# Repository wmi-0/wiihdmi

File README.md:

# wiihdmi
HDMI for your Wii powered by GCVideo

This PCB is based on the popular GCVideo project as well as the Shuriken V3 schematics and features HDMI output (240p, 480i, 480p) for the Wii.
Menu navigation is possible via IR-remote or Gamecube controller.  
One of the main goals for this project was to keep it as cheap as possible.
This means no flex-cable for an easier install, no replacement of analog output (RGB/Component) and most importantly a 2-layer PCB design for cheap manufacturing.

**Consider this project as a beta for now.**  
I've spent several hours testing it on my launch-model Wii, but I'd like to hear some second opinions calling it ready for general use.

## Compatibility
### main_pcb_6_layer
Confirmed to work on RVL-CPU-01 boards.  
The layout possibly fits RVL-CPU-20 as well, but this is currently untested. Won't (properly) fit RVL-CPU-30.  

### main_pcb_4_layer
The new PCB layout is designed for 4-layer Wiis (RVL-CPU-40/50/60) but it's untested as of now.

Both designs use a 2-layer PCB layout which can be manufactured on the cheap, 4/6-layer is just the number of layers used on the intended target Wii mainboard.

## Install
See [GCVideo documentation](https://github.com/ikorb/gcvideo/blob/master/HDL/gcvideo_dvi/README-Wii.md#digital-audio-and-video)

## BOM
### Main PCB
| Designator  | Component |
| ------------- | ------------- |
| U1  | XC3S200A-4VQG100C  |
| U2  | M25P40  |
| U3  | TPS74012DGKR  |
| U4  | IRM-V538/TR1  |
| SW1  | EVQ9P701P  |
| J3  | 15 pin FFC connector 0.5mm pin pitch  |
| C1, C2  | 1 uF, 0805  |
| C3  | 10 uF, 0805  |
| C4-C12  | 0.1 uF, 0805  |
| R1, R3  | 4.7K, 0805  |
| R2  | 330, 0805  |

Use 0603 components for main_pcb_4_layer.

### HDMI PCB
| Designator  | Component |
| ------------- | ------------- |
| J1  | 15 pin FFC connector 0.5mm pin pitch  |
| J2  | Mini-HDMI (Type C) socket  |
| R1  | 180, 0402  |
| R2, R3  | 10K, 0402  |
| U1-U3  | TPD4S010 DQA (optional)  |

Use 0.8mm PCB thickness for both PCBs.

## Todos and next steps
- ~~PCB for 4-layer, 65nm Wii consoles (RVL-CPU-40+)~~
- ~~Provide better install pictures showing the current version of the PCB~~
- Switch to a more common 16 pin FFC instead of 15 pin
- Possibly add half-cut vias as anchor points (the initial design already had some, but the PCB manufacturer charged extra so I removed them again)
- KiCad project cleanup

## Acknowledgements
[ikorb](https://github.com/ikorb): GCVideo project  
[Steven Taffs](http://www.retro-system.com/shuriken%20video.htm): Shuriken V3 schematic and incredibly useful M25P40 programming tool  
[citrus3000psi](https://github.com/citrus3000psi): Inspiration from GCHDMI designs

## License
This project is licensed under the GPL v3.0 License - see the LICENSE.md file for details

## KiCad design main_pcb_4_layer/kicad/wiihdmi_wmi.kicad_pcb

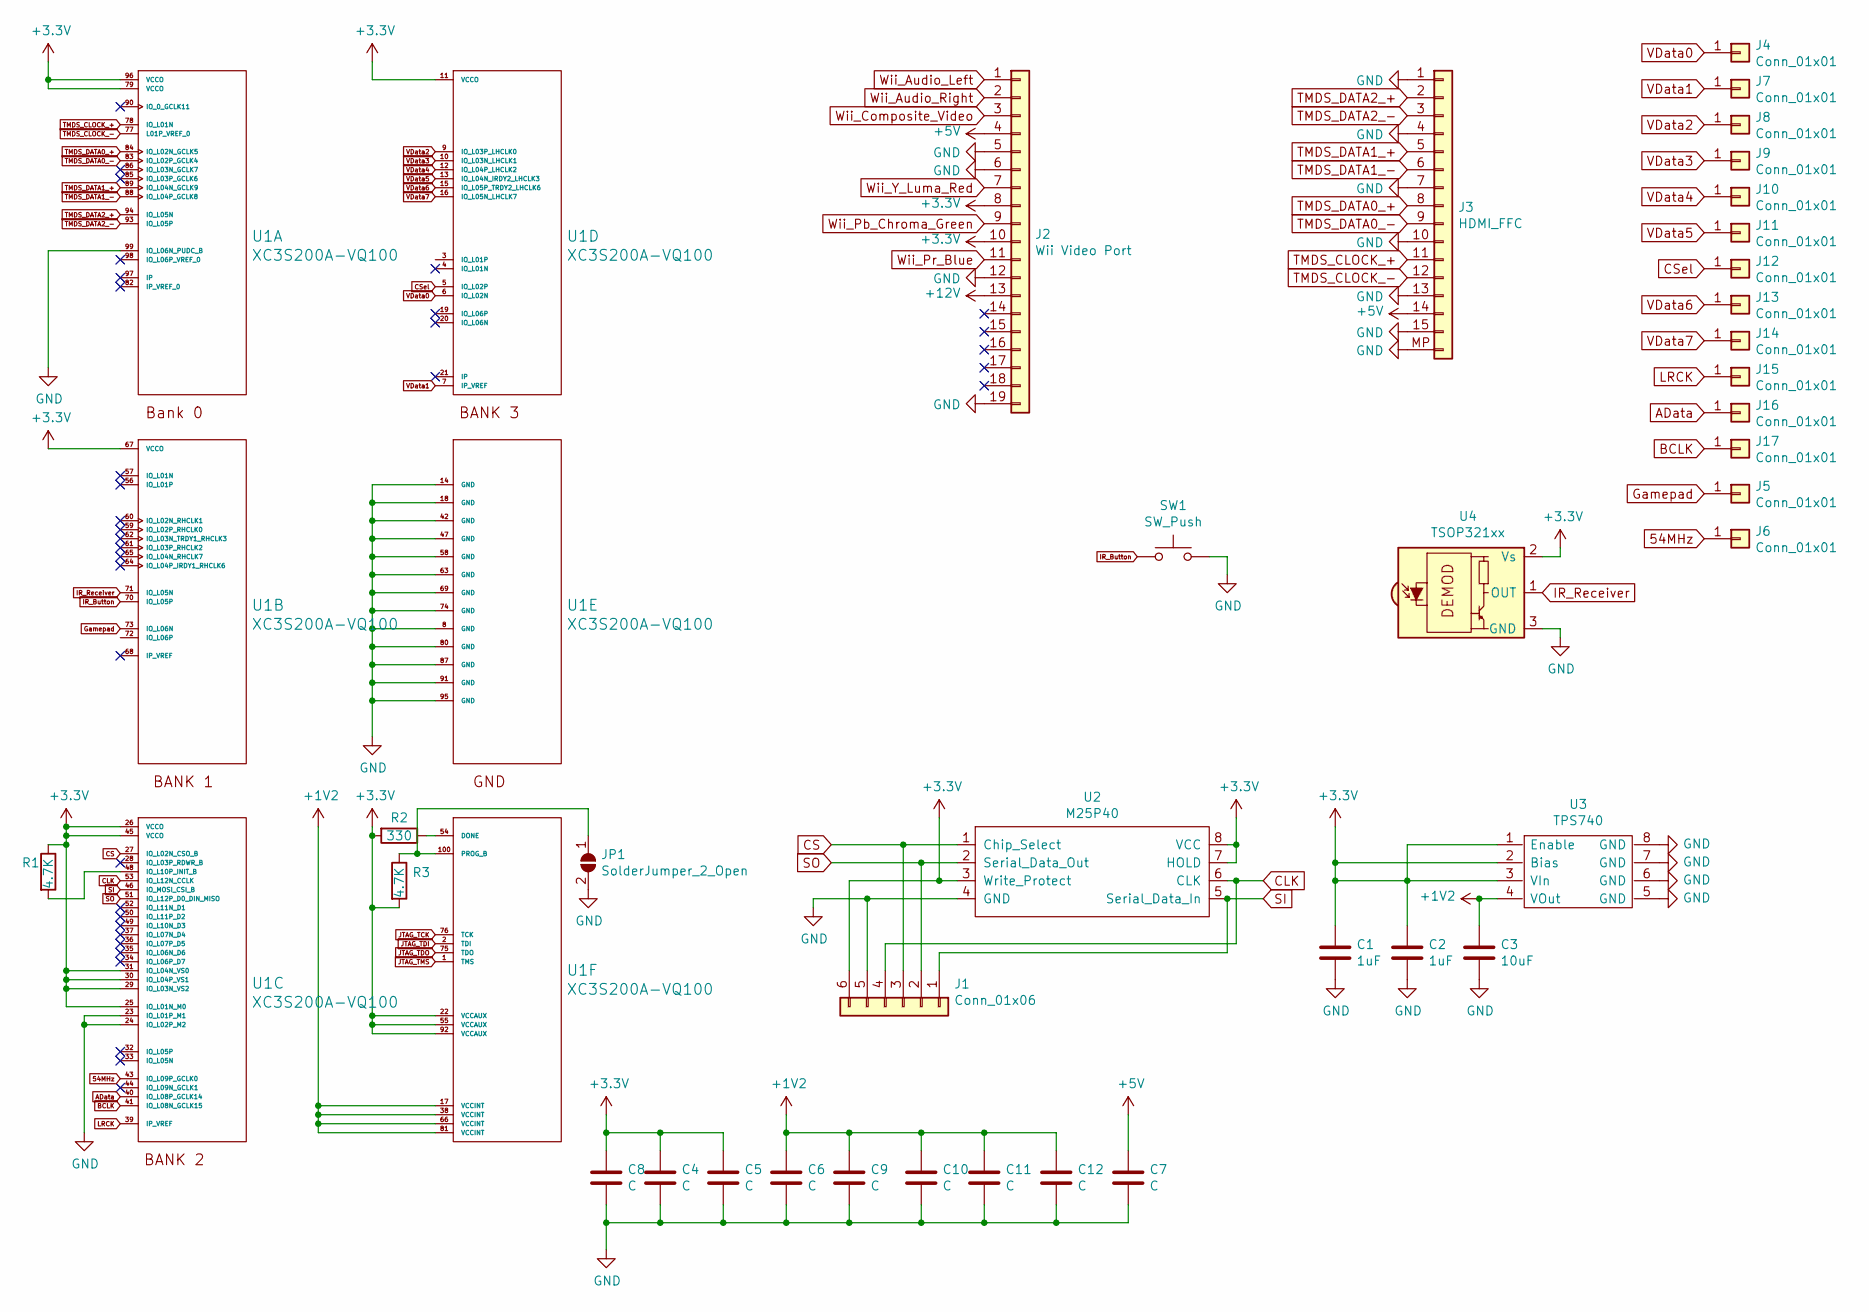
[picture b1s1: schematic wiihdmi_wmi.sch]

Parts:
C1, C2: 1uF; C_0805_2012Metric_Pad1.15x1.40mm_HandSolder
C3: 10uF; C_0805_2012Metric_Pad1.15x1.40mm_HandSolder
C4, C5, C6, C7, C8, C9, C10, C11, C12: C; C_0603_1608Metric_Pad1.05x0.95mm_HandSolder
J1: Conn_01x06; PinHeader_1x06_P1.27mm_Vertical_no_silk
J2: Wii Video Port; Wii AV Port
J3: HDMI_FFC; Hirose_FH12-15S-0.5SH_1x15-1MP_P0.50mm_Horizontal
J4, J5, J6, J7, J8, J9, J10, J11, J12, J13, J14, J15, J16, J17: Conn_01x01; TestPoint_Pad_1.0x1.0mm
JP1: SolderJumper_2_Open; SolderJumper-2_P1.3mm_Open_Pad1.0x1.5mm
R1, R3: 4.7K; R_0603_1608Metric_Pad1.05x0.95mm_HandSolder
R2: 330; R_0603_1608Metric_Pad1.05x0.95mm_HandSolder
SW1: SW_Push; EVQ9P701P
U1: XC3S200A-VQ100; xilinx_spartan3_virtex4_and_5-VQ100
U2: M25P40; SOIC-8_3.9x4.9mm_P1.27mm
U3: TPS740; MSOP-8_3x3mm_P0.65mm
U4: TSOP321xx; IRM-V5xx

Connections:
54MHz: J6.1, U1.43 (IO_L09P_GCLK0)
+1V2: C3.1, C6.1, C9.1, C10.1, C11.1, C12.1, U1.17 (VCCINT), U1.38 (VCCINT), U1.66 (VCCINT), U1.81 (VCCINT), U3.4 (VOut)
+3V3: C1.1, C2.1, C4.1, C5.1, C8.1, J1.6, J2.8, J2.10, R1.1, R2.2, R3.2, U1.11 (VCCO), U1.22 (VCCAUX), U1.25 (IO_L01N_M0), U1.26 (VCCO), U1.29 (IO_L03N_VS2), U1.30 (IO_L04P_VS1), U1.31 (IO_L04N_VS0), U1.45 (VCCO), U1.55 (VCCAUX), U1.67 (VCCO), U1.79 (VCCO), U1.92 (VCCAUX), U1.96 (VCCO), U2.3 (Write_Protect), U2.7 (HOLD), U2.8 (VCC), U3.1 (Enable), U3.2 (Bias), U3.3 (VIn), U4.2 (Vs)
+5V: C7.1, J2.4, J3.14
+12V: J2.13
AData: J16.1, U1.40 (IO_L08P_GCLK14)
BCLK: J17.1, U1.41 (IO_L08N_GCLK15)
CLK: J1.4, U1.53 (IO_L12N_CCLK), U2.6 (CLK)
CS: J1.3, U1.27 (IO_L02N_CSO_B), U2.1 (Chip_Select)
CSel: J12.1, U1.5 (IO_L02P)
GND: C1.2, C2.2, C3.2, C4.2, C5.2, C6.2, C7.2, C8.2, C9.2, C10.2, C11.2, C12.2, J1.5, J2.5, J2.6, J2.12, J2.19, J3.1, J3.4, J3.7, J3.10, J3.13, J3.15, J3.MP (Pin_16), JP1.2 (B), SW1.2, U1.8 (GND), U1.14 (GND), U1.18 (GND), U1.23 (IO_L01P_M1), U1.24 (IO_L02P_M2), U1.42 (GND), U1.47 (GND), U1.58 (GND), U1.63 (GND), U1.69 (GND), U1.74 (GND), U1.80 (GND), U1.87 (GND), U1.91 (GND), U1.95 (GND), U1.99 (IO_L06N_PUDC_B), U2.4 (GND), U3.5 (GND), U3.6 (GND), U3.7 (GND), U3.8 (GND), U4.3 (GND)
Gamepad: J5.1, U1.73 (IO_L06N); also elsewhere on the board
IR_Button: SW1.1, U1.70 (IO_L05P)
IR_Receiver: U1.71 (IO_L05N), U4.1 (OUT)
JTAG_TCK: U1.76 (TCK)
JTAG_TDI: U1.2 (TDI)
JTAG_TDO: U1.75 (TDO)
JTAG_TMS: U1.1 (TMS)
LRCK: J15.1, U1.39 (IP_VREF)
unnamed: JP1.1 (A), R3.1, U1.100 (PROG_B)
unnamed: R1.2, U1.48 (IO_L10P_INIT_B)
unnamed: R2.1, U1.54 (DONE)
SI: J1.1, U1.46 (IO_MOSI_CSI_B), U2.5 (Serial_Data_In)
SO: J1.2, U1.51 (IO_L12P_D0_DIN_MISO), U2.2 (Serial_Data_Out)
TMDS_CLOCK_+: J3.11, U1.78 (IO_L01N)
TMDS_CLOCK_-: J3.12, U1.77 (L01P_VREF_0)
TMDS_DATA0_+: J3.8, U1.84 (IO_L02N_GCLK5)
TMDS_DATA0_-: J3.9, U1.83 (IO_L02P_GCLK4)
TMDS_DATA1_+: J3.5, U1.89 (IO_L04N_GCLK9)
TMDS_DATA1_-: J3.6, U1.88 (IO_L04P_GCLK8)
TMDS_DATA2_+: J3.2, U1.94 (IO_L05N)
TMDS_DATA2_-: J3.3, U1.93 (IO_L05P)
VData0: J4.1, U1.6 (IO_L02N)
VData1: J7.1, U1.7 (IP_VREF)
VData2: J8.1, U1.9 (IO_L03P_LHCLK0)
VData3: J9.1, U1.10 (IO_L03N_LHCLK1)
VData4: J10.1, U1.12 (IO_L04P_LHCLK2)
VData5: J11.1, U1.13 (IO_L04N_IRDY2_LHCLK3)
VData6: J13.1, U1.15 (IO_L05P_TRDY2_LHCLK6)
VData7: J14.1, U1.16 (IO_L05N_LHCLK7)
Wii_Audio_Left: J2.1
Wii_Audio_Right: J2.2
Wii_Composite_Video: J2.3
Wii_Pb_Chroma_Green: J2.9
Wii_Pr_Blue: J2.11
Wii_Y_Luma_Red: J2.7

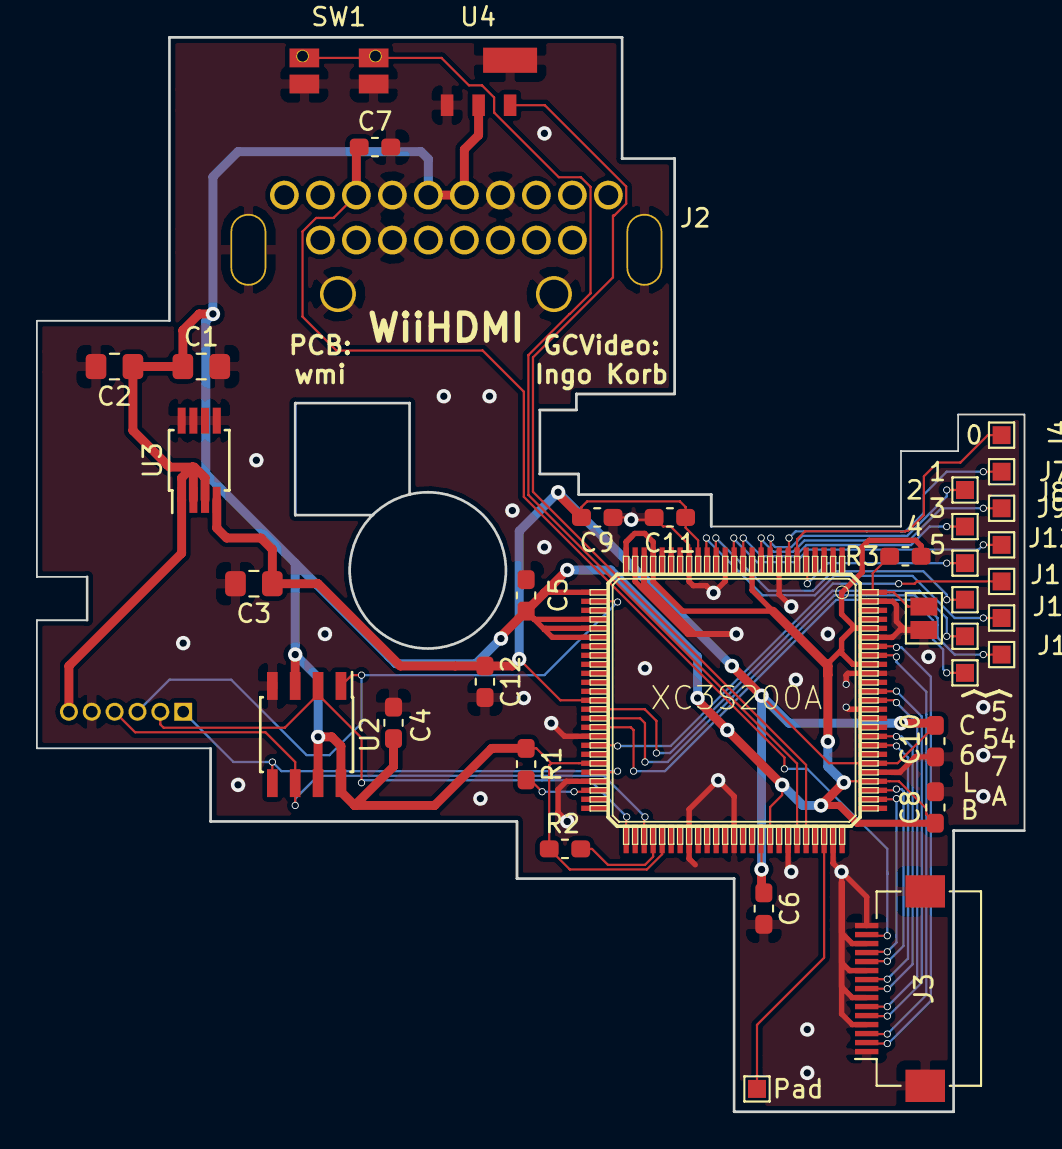
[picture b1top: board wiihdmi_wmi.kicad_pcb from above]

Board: 2 copper layers, 54.9 x 59.7 mm, 38 parts (0 on the bottom side), 35 nets.

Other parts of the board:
Pad: Conn_01x01; TestPoint_Pad_1.0x1.0mm

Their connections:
Gamepad: Pad.1; also elsewhere on the board

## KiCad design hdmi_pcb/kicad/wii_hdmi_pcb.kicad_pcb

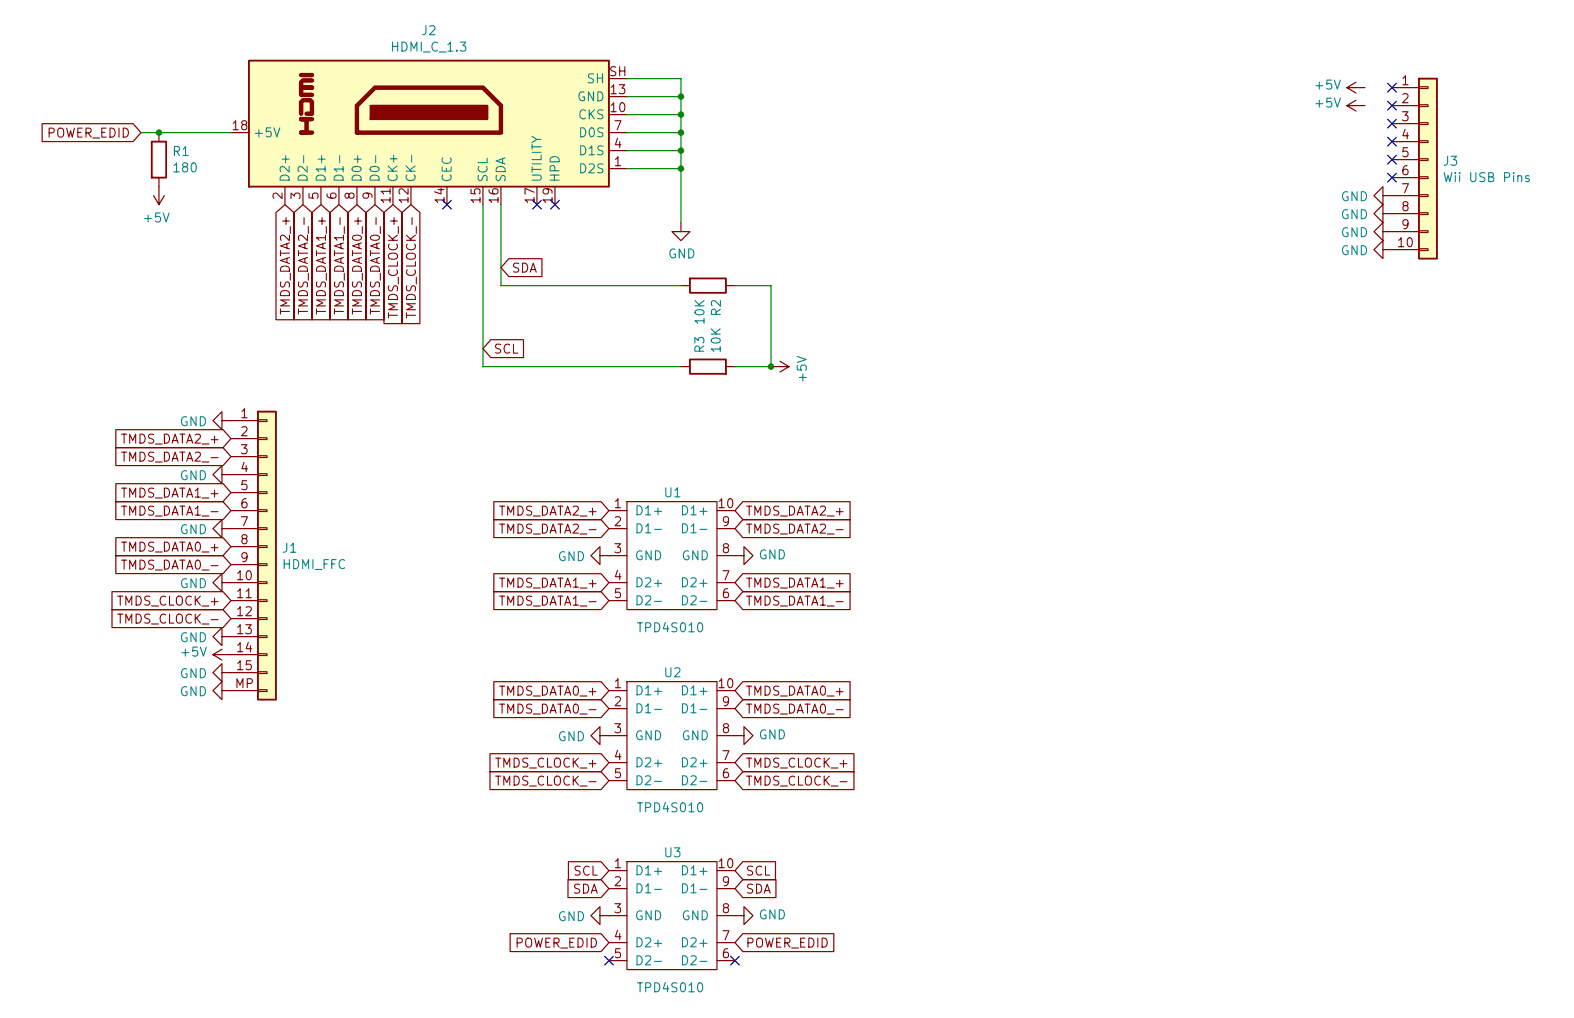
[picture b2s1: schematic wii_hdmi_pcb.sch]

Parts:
J1: HDMI_FFC; Hirose_FH12-15S-0.5SH_1x15-1MP_P0.50mm_Horizontal
J2: HDMI_C_1.3; HDMI Type C
J3: Wii USB Pins; Wii USB Port
R1: 180; R_0402_1005Metric
R2, R3: 10K; R_0402_1005Metric
U1, U2, U3: TPD4S010; TPD4S010 DQA

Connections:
+5V: J1.14, R1.2, R2.1, R3.2
GND: J1.1, J1.4, J1.7, J1.10, J1.13, J1.15, J1.MP (Pin_16), J2.1 (D2S), J2.4 (D1S), J2.7 (D0S), J2.10 (CKS), J2.13 (GND), J2.SH, J3.7, J3.8, J3.9, J3.10, U1.3 (GND), U1.8 (GND), U2.3 (GND), U2.8 (GND), U3.3 (GND), U3.8 (GND)
POWER_EDID: J2.18 (+5V), R1.1, U3.4 (D2+), U3.7 (D2+)
SCL: J2.15 (SCL), R3.1, U3.1 (D1+), U3.10 (D1+)
SDA: J2.16 (SDA), R2.2, U3.2 (D1-), U3.9 (D1-)
TMDS_CLOCK_+: J1.11, J2.11 (CK+), U2.4 (D2+), U2.7 (D2+)
TMDS_CLOCK_-: J1.12, J2.12 (CK-), U2.5 (D2-), U2.6 (D2-)
TMDS_DATA0_+: J1.8, J2.8 (D0+), U2.1 (D1+), U2.10 (D1+)
TMDS_DATA0_-: J1.9, J2.9 (D0-), U2.2 (D1-), U2.9 (D1-)
TMDS_DATA1_+: J1.5, J2.5 (D1+), U1.4 (D2+), U1.7 (D2+)
TMDS_DATA1_-: J1.6, J2.6 (D1-), U1.5 (D2-), U1.6 (D2-)
TMDS_DATA2_+: J1.2, J2.2 (D2+), U1.1 (D1+), U1.10 (D1+)
TMDS_DATA2_-: J1.3, J2.3 (D2-), U1.2 (D1-), U1.9 (D1-)

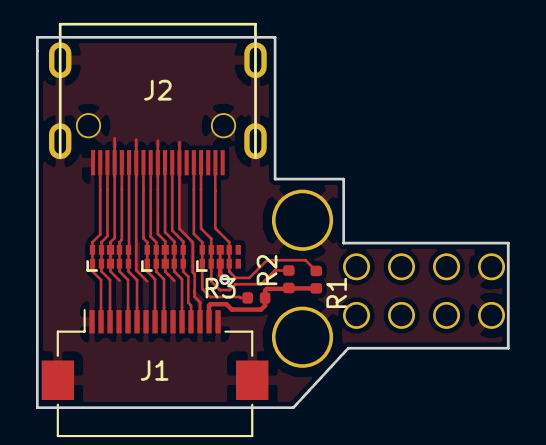
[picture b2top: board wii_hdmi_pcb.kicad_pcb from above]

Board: 2 copper layers, 26.2 x 20.6 mm, 9 parts (0 on the bottom side), 13 nets.

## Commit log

2019-03-10 Added project
2019-03-10 README.md line breaks
2019-04-20 New pictures of current PCB rev
2019-04-20 Added installation guide
2019-04-22 Renamed main_pcb to main_pcb_6_layer
2019-04-22 New PCB variant for 4-layer Wiis
2019-04-22 Updated README.md for 4-layer variant
